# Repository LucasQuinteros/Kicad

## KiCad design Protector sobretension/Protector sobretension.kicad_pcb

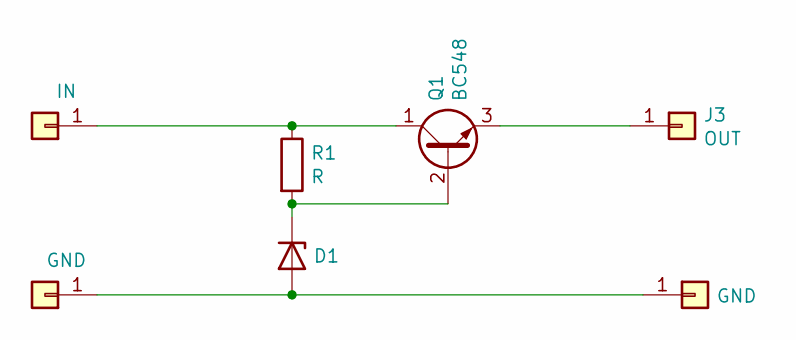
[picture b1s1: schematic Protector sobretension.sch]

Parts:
D1: 1N47xxA; D_DO-41_SOD81_P10.16mm_Horizontal
J1: IN; SolderWire-0.1sqmm_1x01_D0.4mm_OD1mm
J2, J4: GND; SolderWire-0.1sqmm_1x01_D0.4mm_OD1mm
J3: OUT; SolderWire-0.1sqmm_1x01_D0.4mm_OD1mm
Q1: BC548; TO-92_Inline
R1: R; R_Axial_DIN0204_L3.6mm_D1.6mm_P5.08mm_Horizontal

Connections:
unnamed: D1.1 (K), Q1.2 (B), R1.2
unnamed: D1.2 (A), J2.1, J4.1
unnamed: J1.1, Q1.1 (C), R1.1
unnamed: J3.1, Q1.3 (E)

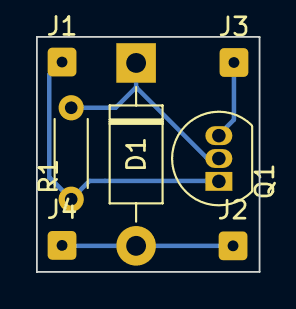
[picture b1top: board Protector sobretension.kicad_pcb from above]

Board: 2 copper layers, 12.4 x 13.1 mm, 7 parts (0 on the bottom side), 4 nets.

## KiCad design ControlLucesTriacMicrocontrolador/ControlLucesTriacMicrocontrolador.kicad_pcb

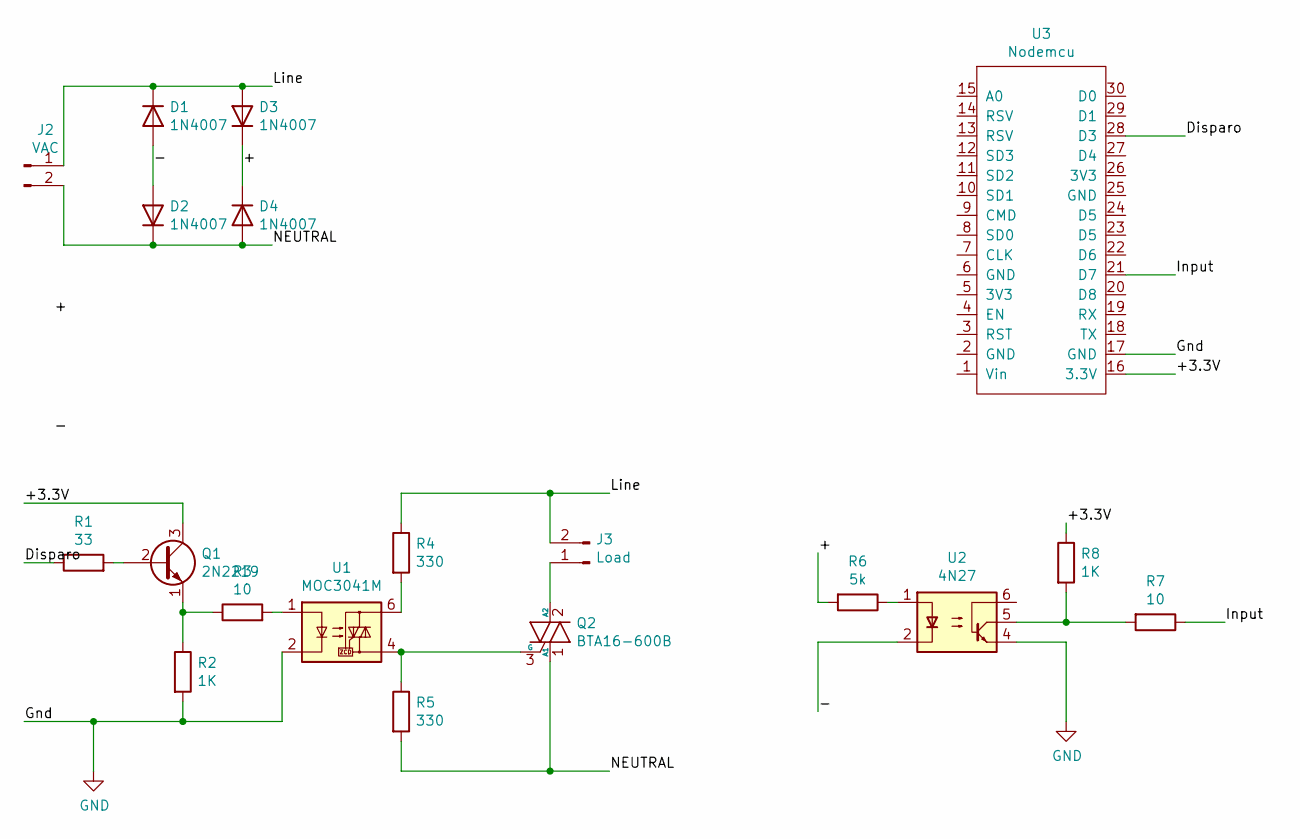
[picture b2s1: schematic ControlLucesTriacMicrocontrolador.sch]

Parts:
D1, D2, D3, D4: 1N4007; D_A-405_P7.62mm_Horizontal
J2: VAC; TerminalBlock_Phoenix_MKDS-1,5-2_1x02_P5.00mm_Horizontal
J3: Load; TerminalBlock_Phoenix_MKDS-1,5-2_1x02_P5.00mm_Horizontal
Q1: 2N2219; TO-39-3
Q2: BTA16-600B; TO-220-3_Vertical
R1: 33; R_Axial_DIN0204_L3.6mm_D1.6mm_P5.08mm_Horizontal
R2, R8: 1K; R_Axial_DIN0204_L3.6mm_D1.6mm_P5.08mm_Horizontal
R3, R7: 10; R_Axial_DIN0204_L3.6mm_D1.6mm_P5.08mm_Horizontal
R4, R5: 330; R_Axial_DIN0204_L3.6mm_D1.6mm_P5.08mm_Horizontal
R6: 5k; R_Axial_DIN0204_L3.6mm_D1.6mm_P5.08mm_Horizontal
U1: MOC3041M; DIP-6_W7.62mm
U2: 4N27; DIP-6_W7.62mm
U3: Nodemcu

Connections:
/+: D3.1 (K), D4.1 (K), R6.2
/+3.3V: Q1.3 (C), R8.1, U3.16 (3.3V)
/-: D1.2 (A), D2.2 (A), U2.2
/Disparo: R1.1, U3.28 (D3)
/Input: R7.1, U3.21 (D7)
/Line: D1.1 (K), D3.2 (A), J2.1, J3.2, R4.1
/NEUTRAL: D2.1 (K), D4.2 (A), J2.2, Q2.1 (A1), R5.2
GND: R2.2, U1.2, U2.4, U3.17 (GND); also elsewhere on the board
unnamed: J3.1, Q2.2 (A2)
unnamed: Q1.1 (E), R2.1, R3.1
unnamed: Q1.2 (B), R1.2
unnamed: Q2.3 (G), R5.1, U1.4
unnamed: R3.2, U1.1
unnamed: R4.2, U1.6
unnamed: R6.1, U2.1
unnamed: R7.2, R8.2, U2.5

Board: 2 copper layers, 22 parts (0 on the bottom side), 16 nets, no tracks yet.

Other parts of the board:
+3.3V1: Conn_01x01_Male; PinHeader_1x01_P1.00mm_Vertical
Input1: Conn_01x01_Male; PinHeader_1x01_P1.00mm_Vertical
J1: +3.3V Vdisparo GND; TerminalBlock_Phoenix_MKDS-1,5-3_1x03_P5.00mm_Horizontal

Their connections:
GND: J1.3; also elsewhere on the board

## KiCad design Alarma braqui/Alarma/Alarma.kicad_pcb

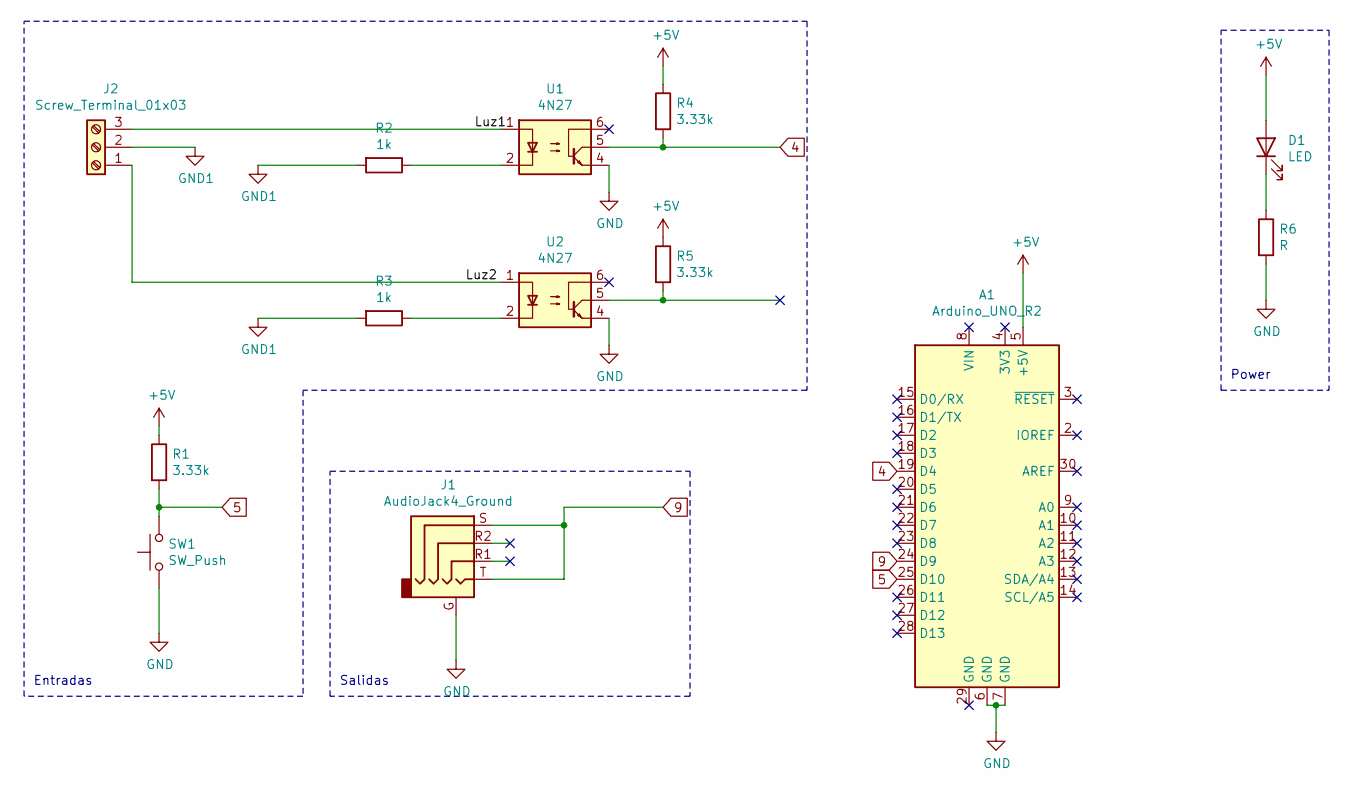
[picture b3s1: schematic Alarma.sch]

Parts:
A1: Arduino_UNO_R2; Arduino_UNO_R2_WithMountingHoles
D1: LED; LED_D3.0mm
J1: AudioJack4_Ground; Tayda_3.5mm_stereo_TRS_jack_A-853
J2: Screw_Terminal_01x03; TerminalBlock_Phoenix_MKDS-1,5-3-5.08_1x03_P5.08mm_Horizont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
R1, R4, R5: 3.33k; R_Axial_DIN0204_L3.6mm_D1.6mm_P7.62mm_Horizontal
R2, R3: 1k; R_Axial_DIN0204_L3.6mm_D1.6mm_P7.62mm_Horizontal
R6: R; R_Axial_DIN0204_L3.6mm_D1.6mm_P5.08mm_Horizontal
SW1: SW_Push; SW_PUSH_6mm
U1, U2: 4N27; DIP-6_W7.62mm

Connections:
4: A1.19 (D4), R4.2, U1.5
5: A1.25 (D10), R1.2, SW1.2
9: A1.24 (D9), J1.S, J1.T
+5V: A1.5 (+5V), D1.2 (A), R1.1, R4.1, R5.1
/Luz1: J2.3, U1.1
/Luz2: J2.1, U2.1
GND: A1.6 (GND), A1.7 (GND), J1.G, R6.2, SW1.1, U1.4, U2.4
GND1: J2.2, R2.2, R3.2
unnamed: D1.1 (K), R6.1
unnamed: R2.1, U1.2
unnamed: R3.1, U2.2
unnamed: R5.2, U2.5

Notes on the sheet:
Entradas
Salidas
Power

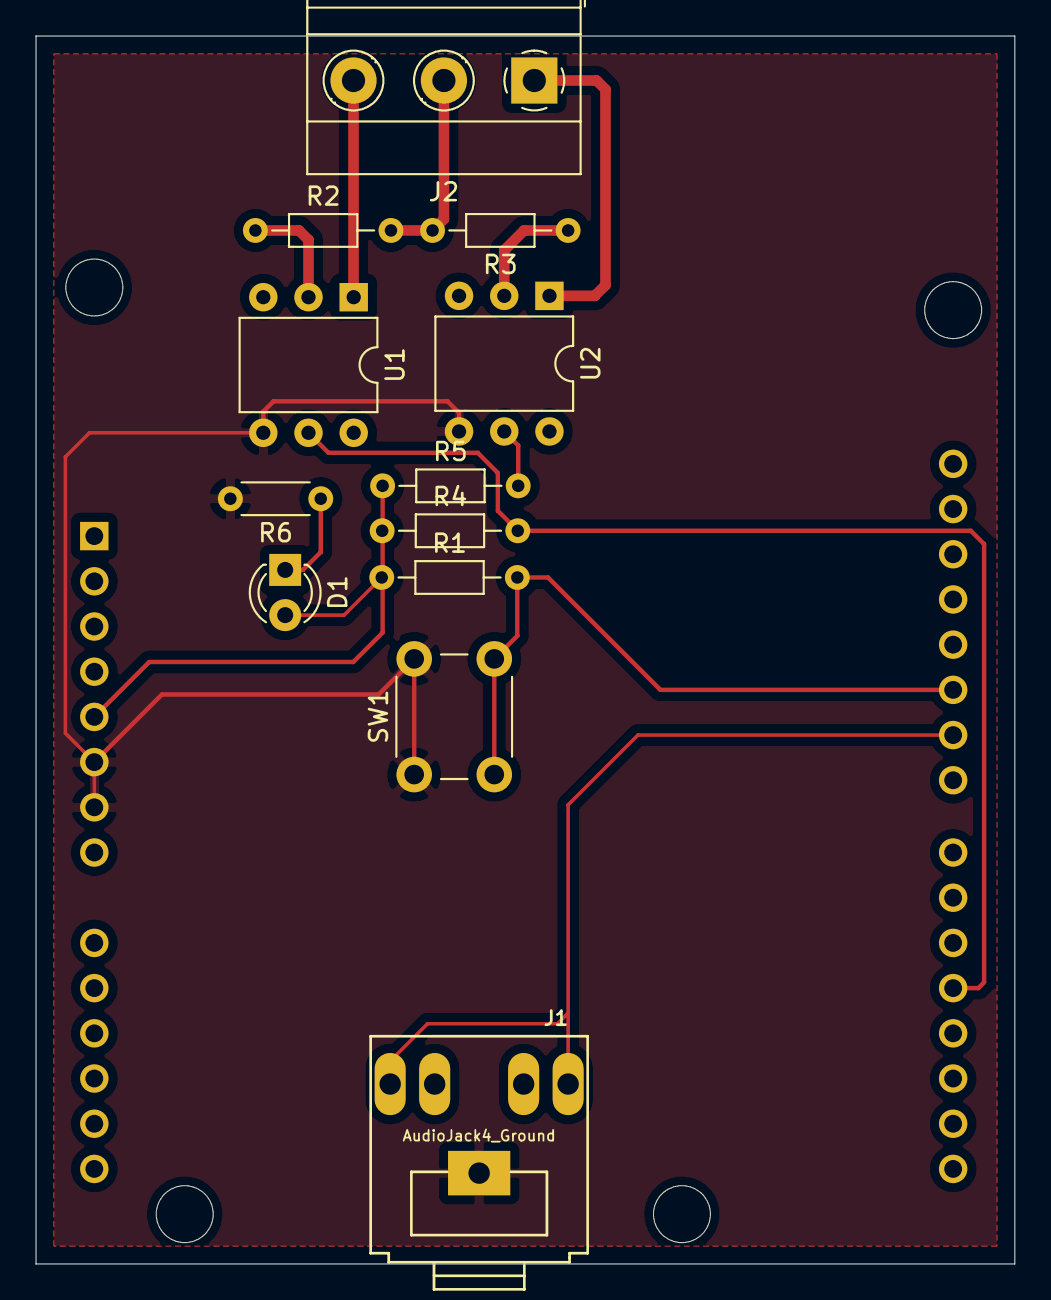
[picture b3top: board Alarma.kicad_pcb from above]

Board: 2 copper layers, 55.0 x 69.0 mm, 13 parts (1 on the bottom side), 12 nets.

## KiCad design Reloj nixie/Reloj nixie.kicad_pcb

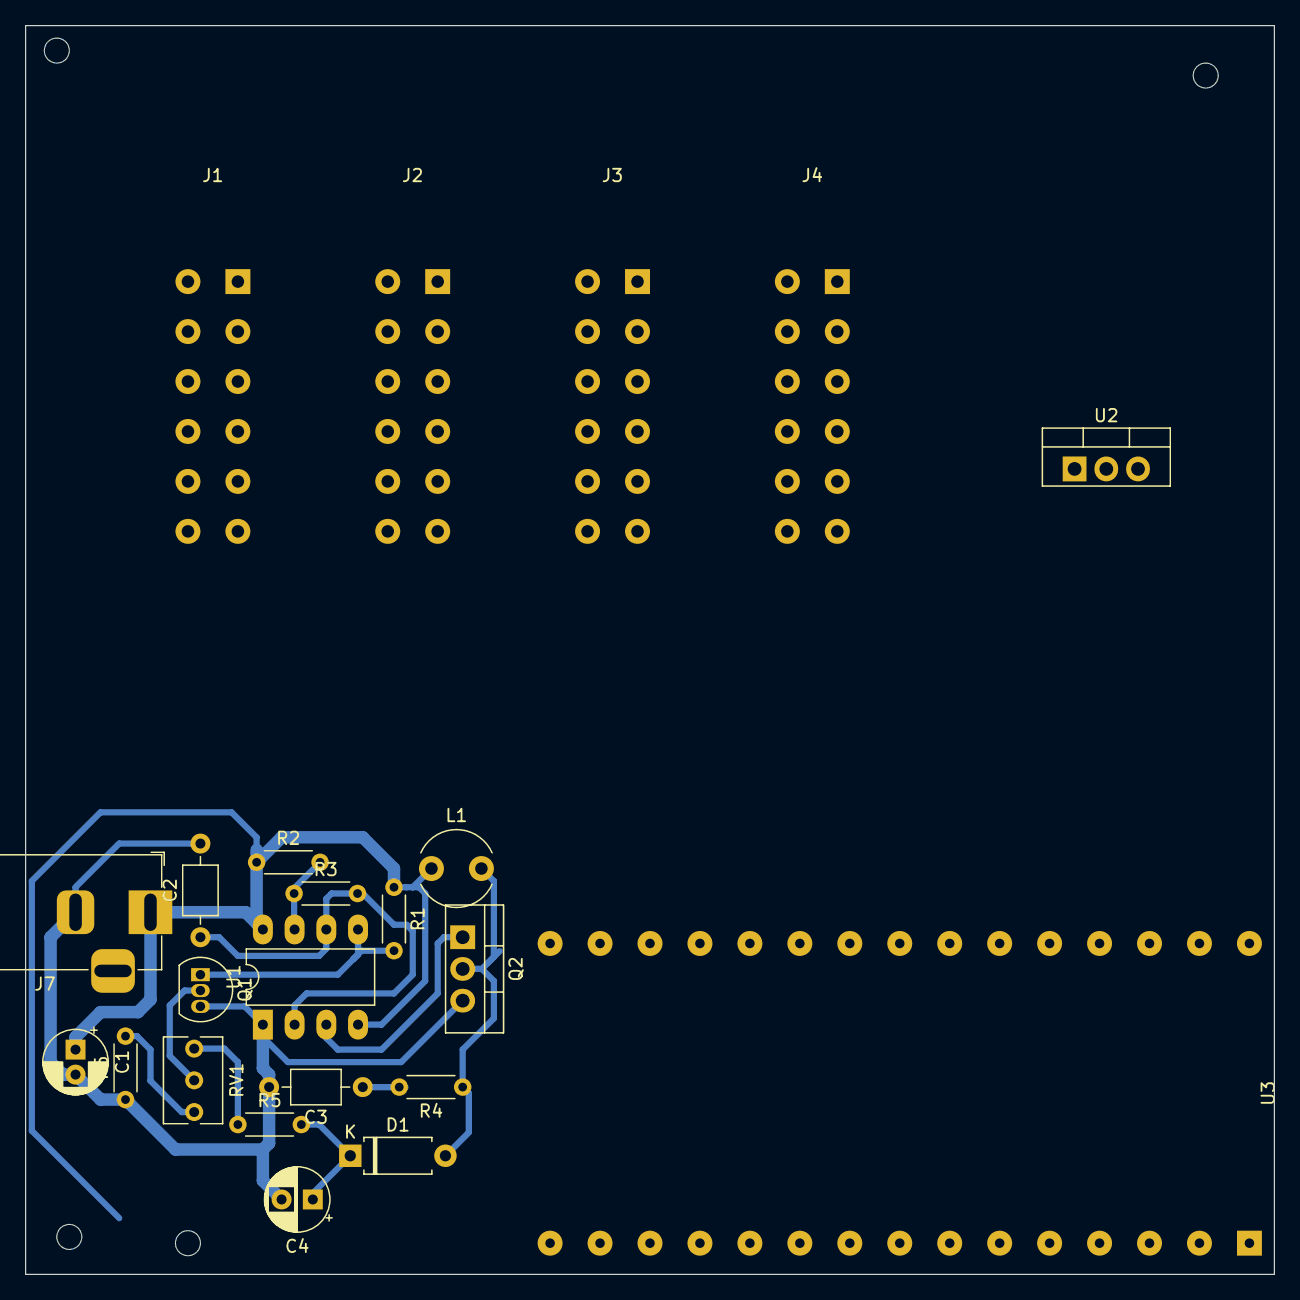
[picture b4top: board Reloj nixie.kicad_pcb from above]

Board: 2 copper layers, 100.0 x 100.0 mm, 23 parts (0 on the bottom side), 13 nets.

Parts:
C1: 330uF; CP_Radial_D5.0mm_P2.00mm
C2: 2.2nF; C_Axial_L3.8mm_D2.6mm_P7.50mm_Horizontal
C3: 100pF; C_Axial_L3.8mm_D2.6mm_P7.50mm_Horizontal
C4: 2.2uF; CP_Radial_D5.0mm_P2.50mm
D1: UF4004; D_A-405_P7.62mm_Horizontal
J1, J2, J3, J4: Conn_02x06_Nixie; Conector_zocalo
J7: Barrel_Jack_MountingPin; BarrelJack_Horizontal
L1: 100uH; L_Radial_D6.0mm_P4.00mm
Q1: BC547; TO-92L_Inline
Q2: IRF740; TO-220-3_Vertical
R1: 56K; R_Axial_DIN0204_L3.6mm_D1.6mm_P5.08mm_Horizontal
R2: 1K; R_Axial_DIN0204_L3.6mm_D1.6mm_P5.08mm_Horizontal
R3: 10K; R_Axial_DIN0204_L3.6mm_D1.6mm_P5.08mm_Horizontal
R4: 2.2K; R_Axial_DIN0204_L3.6mm_D1.6mm_P5.08mm_Horizontal
R5: 220K; R_Axial_DIN0204_L3.6mm_D1.6mm_P5.08mm_Horizontal
R6: 470; R_Axial_DIN0204_L3.6mm_D1.6mm_P5.08mm_Horizontal
RV1: 1K; Potentiometer_Bourns_3266Y_Vertical
U1: NE555P; DIP-8_W7.62mm_LongPads
U2: LM7805_TO220; TO-220-3_Vertical
U3: Nodemcu

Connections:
unnamed: C1.1, J7.1, L1.1, R1.1, R2.1, U1.4, U1.8, U2.1
unnamed: C1.2, C2.2, C3.2, C4.2, J4.A, J7.2, Q1.3, Q2.3, R6.1, U1.1, U2.2, U3.2
unnamed: C2.1, R3.2, U1.2, U1.6
unnamed: C3.1, R4.2
unnamed: C4.1, D1.1, J4.1, R5.2
unnamed: D1.2, L1.2, Q2.2, R4.1
unnamed: J4.2, U2.3, U3.1
unnamed: Q1.1, R1.2, U1.5
unnamed: Q1.2, RV1.2
unnamed: Q2.1, U1.3
unnamed: R2.2, R3.1, U1.7
unnamed: R5.1, RV1.3
unnamed: R6.2, RV1.1

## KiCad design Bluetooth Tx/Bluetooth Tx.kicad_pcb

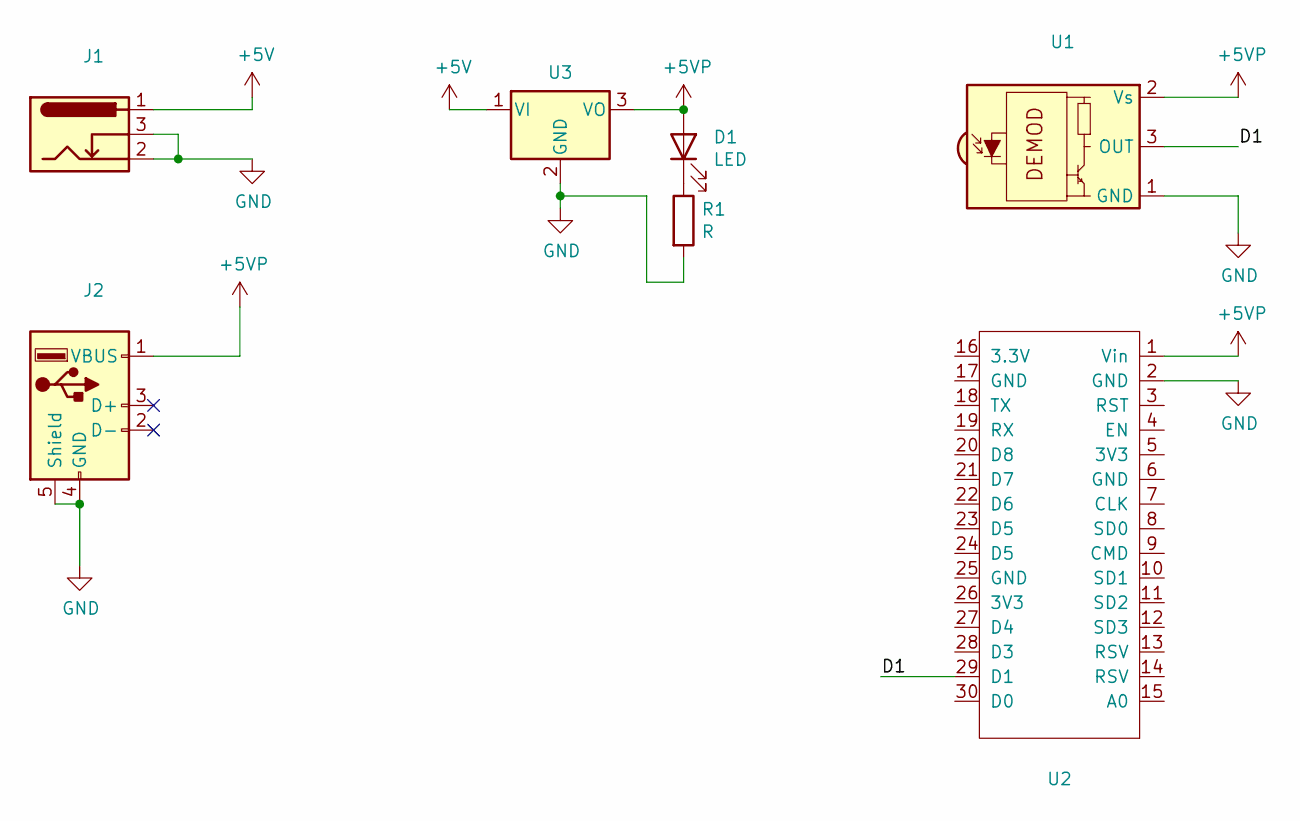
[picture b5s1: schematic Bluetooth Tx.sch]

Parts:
D1: LED; LED_D3.0mm
J1: Barrel_Jack_Switch; BarrelJack_Horizontal
J2: USB_A; USB_A_Molex_105057_Vertical
R1: R; R_Axial_DIN0204_L3.6mm_D1.6mm_P7.62mm_Horizontal
U1: TSOP17xx; Vishay_MINICAST-3Pin
U2: Nodemcu
U3: LM7805_TO220; TO-220-3_Vertical

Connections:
+5V: J1.1, U3.1 (VI)
+5VP: D1.2 (A), J2.1 (VBUS), U1.2 (Vs), U2.1 (Vin), U3.3 (VO)
/D1: U1.3 (OUT), U2.29 (D1)
GND: J1.2, J1.3, J2.4 (GND), J2.5 (Shield), R1.2, U1.1 (GND), U2.2 (GND), U3.2 (GND)
unnamed: D1.1 (K), R1.1

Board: 2 copper layers, 7 parts (0 on the bottom side), 5 nets, no tracks yet.

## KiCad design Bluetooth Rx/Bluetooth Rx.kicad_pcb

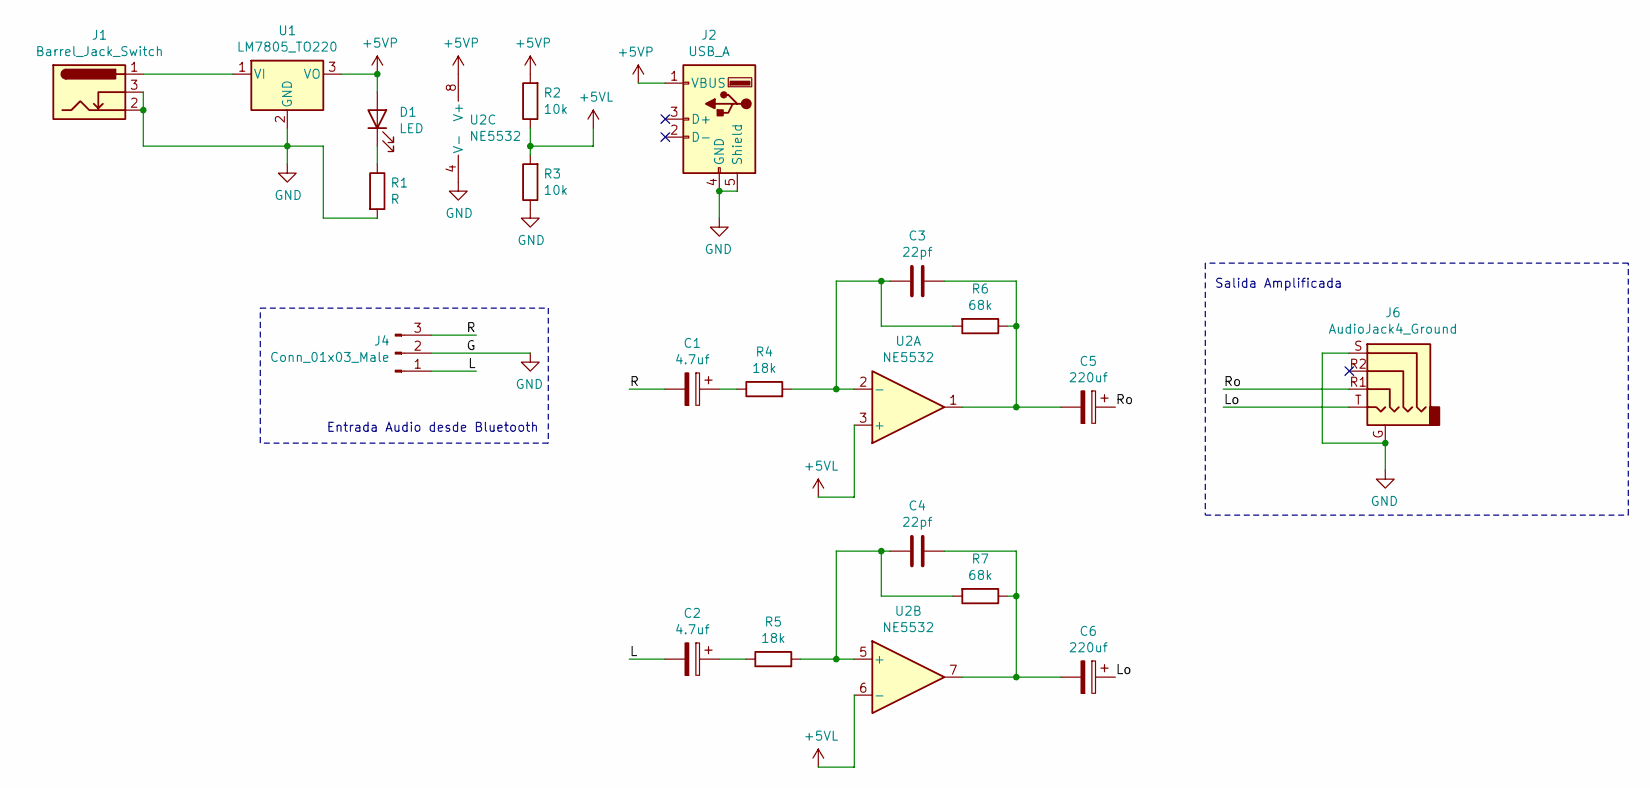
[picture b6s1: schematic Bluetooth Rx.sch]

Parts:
C1, C2: 4.7uf; CP_Radial_Tantal_D6.0mm_P2.50mm
C3, C4: 22pf; C_Axial_L3.8mm_D2.6mm_P7.50mm_Horizontal
C5, C6: 220uf; CP_Radial_Tantal_D6.0mm_P2.50mm
D1: LED; LED_D3.0mm
J1: Barrel_Jack_Switch; BarrelJack_Horizontal
J2: USB_A; USB_A_Molex_105057_Vertical
J4: Conn_01x03_Male; PinHeader_1x03_P2.00mm_Vertical
J6: AudioJack4_Ground; Tayda_3.5mm_stereo_TRS_jack_A-853
R1: R; R_Axial_DIN0204_L3.6mm_D1.6mm_P7.62mm_Horizontal
R2, R3: 10k; R_Axial_DIN0204_L3.6mm_D1.6mm_P5.08mm_Horizontal
R4, R5: 18k; R_Axial_DIN0204_L3.6mm_D1.6mm_P5.08mm_Horizontal
R6, R7: 68k; R_Axial_DIN0204_L3.6mm_D1.6mm_P5.08mm_Horizontal
U1: LM7805_TO220; TO-220F-3_Horizontal_TabDown
U2: NE5532; DIP-8_W7.62mm_Socket_LongPads

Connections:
+5VL: R2.1, R3.2, U2.3 (+), U2.6 (-)
+5VP: D1.2 (A), J2.1 (VBUS), R2.2, U1.3 (VO), U2.8 (V+)
/L: C2.2, J4.1
/Lo: C6.1, J6.T
/R: C1.2, J4.3
/Ro: C5.1, J6.R1
GND: J1.2, J1.3, J2.4 (GND), J2.5 (Shield), J4.2, J6.G, J6.S, R1.2, R3.1, U1.2 (GND), U2.4 (V-)
unnamed: C1.1, R4.1
unnamed: C2.1, R5.1
unnamed: C3.1, C5.2, R6.1, U2.1
unnamed: C3.2, R4.2, R6.2, U2.2 (-)
unnamed: C4.1, C6.2, R7.1, U2.7
unnamed: C4.2, R5.2, R7.2, U2.5 (+)
unnamed: D1.1 (K), R1.1
unnamed: J1.1, U1.1 (VI)

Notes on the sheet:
Entrada Audio desde Bluetooth
Salida Amplificada

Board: 2 copper layers, 20 parts (0 on the bottom side), 15 nets, no tracks yet.
